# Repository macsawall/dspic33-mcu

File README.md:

# dspic33-mcu
Assorted implemented features for the dspic33ev256gm102 microcontroller.

Robotic arm video:
https://drive.google.com/file/d/13MOty1gT1kS0LDJHBQBNm70005ARxoOs/view?usp=sharing

dspic33 Development Board CCA:
https://drive.google.com/drive/folders/1rH_9bEHngeySth9yQ-QKCI5J5p1dckLf?usp=sharing

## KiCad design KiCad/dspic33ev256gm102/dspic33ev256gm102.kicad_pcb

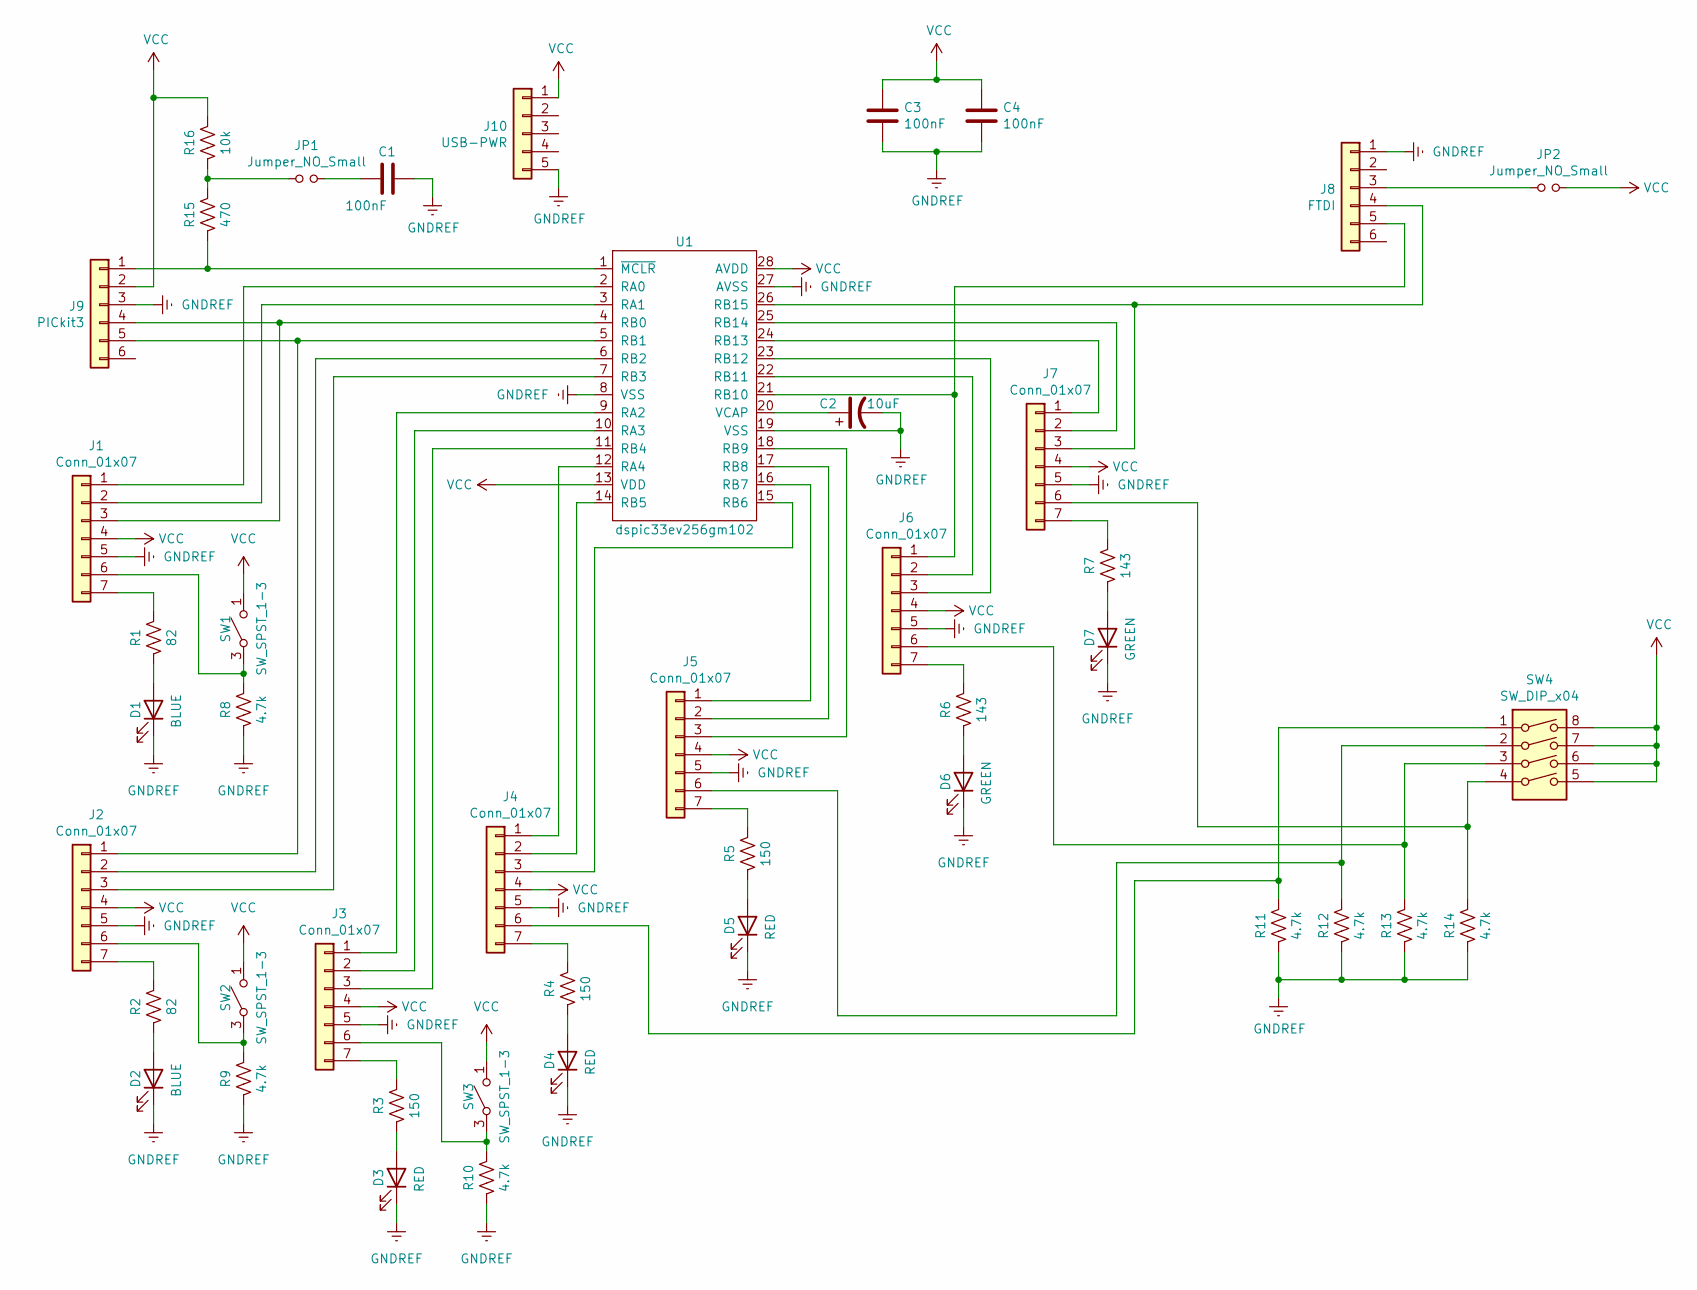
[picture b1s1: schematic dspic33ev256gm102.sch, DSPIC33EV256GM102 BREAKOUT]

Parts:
C1, C3, C4: 100nF; C_0603_1608Metric
C2: 10uF; C_1206_3216Metric
D1, D2: BLUE; LED_0603_1608Metric
D3, D4, D5: RED; LED_0603_1608Metric
D6, D7: GREEN; LED_0603_1608Metric
J1, J2, J3, J4, J5, J6, J7: Conn_01x07; PinHeader_1x07_P2.54mm_Vertical
J8: FTDI; PinHeader_1x06_P2.54mm_Vertical_SMD_Pin1Right
J9: PICkit3; PinHeader_1x06_P2.54mm_Vertical_SMD_Pin1Right
J10: USB-PWR; PinHeader_1x05_P2.54mm_Vertical
JP1, JP2: Jumper_NO_Small; R_0603_1608Metric
R1, R2: 82; R_0603_1608Metric
R3, R4, R5: 150; R_0603_1608Metric
R6, R7: 143; R_0603_1608Metric
R8, R9, R10, R11, R12, R13, R14: 4.7k; R_0603_1608Metric
R15: 470; R_0603_1608Metric
R16: 10k; R_0603_1608Metric
SW1, SW2, SW3: SW_SPST_1-3; Switch_Tactile_SMD_6x6mm
SW4: SW_DIP_x04; SW_DIP_SPSTx04_Slide_6.7x11.72mm_W8.61mm_P2.54mm_LowProfile
U1: dspic33ev256gm102; SSOP-28_5.3x10.2mm_P0.65mm

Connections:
GNDREF: C1.2, C2.2, C3.2, C4.2, D1.1 (K), D2.1 (K), D3.1 (K), D4.1 (K), D5.1 (K), D6.1 (K), D7.1 (K), J1.5, J2.5, J3.5, J4.5, J5.5, J6.5, J7.5, J8.1, J9.3, J10.5, R8.1, R9.1, R10.1, R11.1, R12.1, R13.1, R14.1, U1.8 (VSS), U1.19 (VSS), U1.27 (AVSS)
unnamed: C1.1, JP1.2
unnamed: C2.1, U1.20 (VCAP)
unnamed: D1.2 (A), R1.1
unnamed: D2.2 (A), R2.1
unnamed: D3.2 (A), R3.1
unnamed: D4.2 (A), R4.1
unnamed: D5.2 (A), R5.1
unnamed: D6.2 (A), R6.1
unnamed: D7.2 (A), R7.1
unnamed: J1.1, U1.2 (RA0)
unnamed: J1.2, U1.3 (RA1)
unnamed: J1.3, J9.4, U1.4 (RB0)
unnamed: J1.6, R8.2, SW1.3 (A)
unnamed: J1.7, R1.2
unnamed: J2.1, J9.5, U1.5 (RB1)
unnamed: J2.2, U1.6 (RB2)
unnamed: J2.3, U1.7 (RB3)
unnamed: J2.6, R9.2, SW2.3 (A)
unnamed: J2.7, R2.2
unnamed: J3.1, U1.9 (RA2)
unnamed: J3.2, U1.10 (RA3)
unnamed: J3.3, U1.11 (RB4)
unnamed: J3.6, R10.2, SW3.3 (A)
unnamed: J3.7, R3.2
unnamed: J4.1, U1.12 (RA4)
unnamed: J4.2, U1.14 (RB5)
unnamed: J4.3, U1.15 (RB6)
unnamed: J4.6, R11.2, SW4.1
unnamed: J4.7, R4.2
unnamed: J5.1, U1.16 (RB7)
unnamed: J5.2, U1.17 (RB8)
unnamed: J5.3, U1.18 (RB9)
unnamed: J5.6, R12.2, SW4.2
unnamed: J5.7, R5.2
unnamed: J6.1, J8.5, U1.21 (RB10)
unnamed: J6.2, U1.22 (RB11)
unnamed: J6.3, U1.23 (RB12)
unnamed: J6.6, R13.2, SW4.3
unnamed: J6.7, R6.2
unnamed: J7.1, U1.24 (RB13)
unnamed: J7.2, U1.25 (RB14)
unnamed: J7.3, J8.4, U1.26 (RB15)
unnamed: J7.6, R14.2, SW4.4
unnamed: J7.7, R7.2
unnamed: J8.3, JP2.1
unnamed: J9.1, R15.1, U1.1 (~MCLR)
unnamed: JP1.1, R15.2, R16.1
VCC: C3.1, C4.1, J1.4, J2.4, J3.4, J4.4, J5.4, J6.4, J7.4, J9.2, J10.1, JP2.2, R16.2, SW1.1 (B), SW2.1 (B), SW3.1 (B), SW4.5, SW4.6, SW4.7, SW4.8, U1.13 (VDD), U1.28 (AVDD)

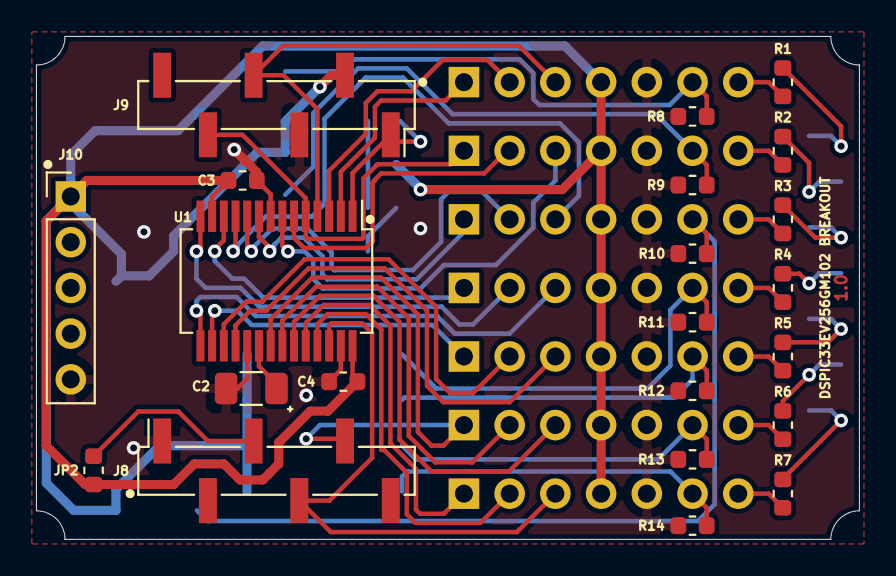
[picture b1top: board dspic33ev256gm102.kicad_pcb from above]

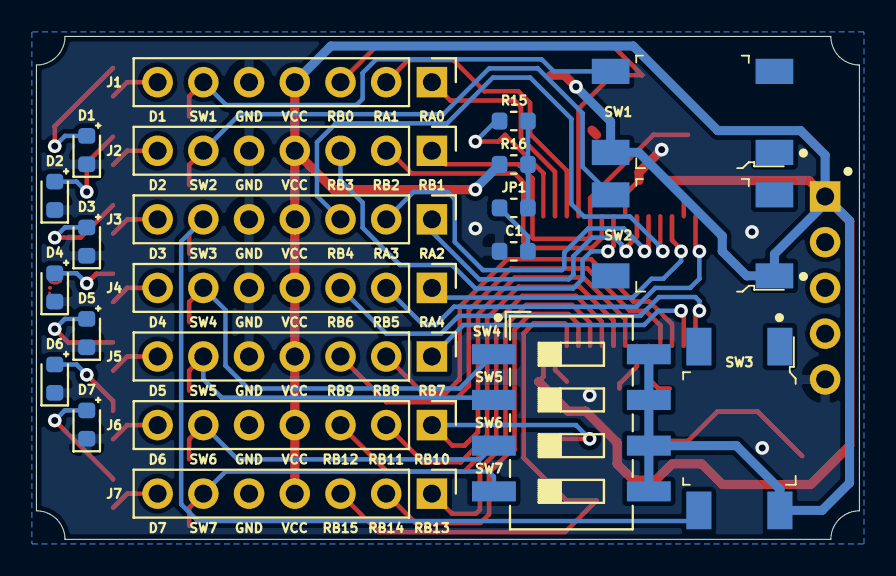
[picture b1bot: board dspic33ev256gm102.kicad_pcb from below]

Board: 2 copper layers, 45.7 x 27.9 mm, 44 parts (22 on the bottom side), 49 nets.

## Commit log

2020-02-23 modified readme
2020-02-23 More and more edits to readme
2020-02-23 Removed edits to readme
2020-02-23 modified readme in master
2020-02-23 fixed readme
2020-02-26 Copied in existing UART-LCD project
2020-02-26 Removed LCD code from project main file, leaving only uart; Removed while loop from rx isr
2020-02-26 converted tabs to 2 spaces
2020-02-26 added a docs folder with all dspic33 manuals
2020-02-26 created a projects folder for storing projects
2020-02-27 Fixed uart.x so that received bytes can be passed to uart_tx() as a string; Also reorganized the docs directory
2020-02-27 Changed doc file names
2020-03-01 cleaned up old comments in main.c
2020-03-01 added sw_testing folder
2020-03-04 initial commit of new project spi-lcd
2020-03-04 Put delay back in spi-lcd to give it time to boot up before sending it commands
2020-03-09 added sw test files
2021-11-13 Fixes
2021-11-13 readme update
2021-11-13 added KiCad PCB project and removed sw testing folder
2021-11-13 added senior design source files
2021-11-13 added robotic arm project
2021-11-14 added pdf schematic of dev board cca
2021-11-14 added missing custom library files
